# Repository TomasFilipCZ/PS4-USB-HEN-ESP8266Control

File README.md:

<h1 align="center">PS4 USB HEN Controlled by ESP8266</h1>

<p>Small electronic board to support automatic loading HEN in PS4 with ESP8266. Project using method discovered on PS4 Firmware 9.00, where user need manually plug USB flash drive in right time to load HEN. 

Together with  ESP8266 as WebServer is PS4-USB-HEN  controlling power supply for USB drive, causing automatic loading HEN in desired time without user interaction.  

Project is modification of "PS4 Server 9.00", aim is to share design data of small PCB to create device for wide  usage of automatic loading and implement basic electronic protection for PS4.  </p>

<i>Status</i>
<b> 23.01.2022 waiting for PCB from production to add more picture and check design files !</b>

## Project requirements
- [ Wemos ESP8266 Mini Board ](https://www.wemos.cc/en/latest/d1/d1_mini_lite.html "v3.00") or any available clone supporting 4MB Flash, recommend is use version V3 with mounting holes as listed in pictures section below
- any working USB 2.0 Flash Disk ( size basically not matter >128MBytes, USB3.0 is not required)
-  Micro USB 2.0 data cable ( is recommend to not exceed length of 1.8M )

## Links
ESP8266 needs firmware to run WebServer with DHCP/DNS service, it can be found here:
- Either compile slight mod of PS4-Server-900 with USB Auto mount feature [PS4-Server-900u](https://github.com/stooged/PS4-Server-900u "<project-name>use pico-exfat")
or download binary file "ESP8266 Auto mount USB 900NA.bin"  from [compiled version by Karo (Twitter karo_sharifi ) ](https://t.co/9buavulD5x "900u.bin")

USB Drive for PS4-USB-HEN needs to be properly installed with ChendoChap Kernel Exploit 
- [ChendoChap PS4 9.00 Kernel Exploit](https://github.com/ChendoChap/pOOBs4 "pico-exfat")

## Setup
- Setup once USB Flash disk
Instructions can be found on ChendoChap PS4 GitHub or generally on internet, alternatively to Win32Disk Imager can be recommend [Rufus utility](https://rufus.ie/en/ "Rufus")   in both solution choose as USB Image  <b>exfathax_pico.img file</b>. 

- Setup once ESP8266
Either by Arduino IDE or [NodeMCU-PyFlasher](https://github.com/marcelstoer/nodemcu-pyflasher/releases), manual for programming ESP8266 with USB cable with PC can be find easily on internet. (with USB cable plug into ESP8266 board)

- Plug ESP8266 Board into PS4-USB-HEN, micro USB cable to PS4 and PS4-USB_HEN micro USB port. Due Webserver/DNS capability of ESP8266 web page with HEN  can be access through 'User Guide/Helpful Info' in PS4  <i>(required successful Wifi connection to ESP8266, if is not changed, access point is 'PS4_WEB_AP' , password is 'password' or '12345678</i> )

## Pictures

## Project structure

- PCB Design data are developed in KiCad 5.1.10
- directory <b>bom</b> contains JLCPCB compatible BOM and BOM with MPN parts, including order codes from [TME.EU](https://tme.eu)
- directory <b>gerber</b> contains gerbers files with pick-up place file. Components are located only in TOP layer. USB A connector hasn't defined positions because is THT. 
- directory <b>libs </b> contains project specific  library special thanks to [ Raoul Rubien, for library for Wemos D1 Mini]( https://github.com/rubienr/wemos-d1-mini-kicad) and [ Fork Sand Devloper ](https://gitlab.com/forksand-dev1) for 3Dmodel of USB-A connector

## Future Updates

- [ ] Create STEP/STL Model of Plastic BOX to be able printed in 3D Printer
- [ ] Waiting for Delivering PCB to test all complete designs - <b> design is not tested YET! </b>

## Author

**Tomas Filip**

- [Profile](https://github.com/TomasFilipCZ "Tomas Filip on GitHub")
- [Join us on Discord](https://discord.gg/DWephJvzwR "Discord Server")

## 🤝 Support

Contributions, issues, and feature requests are welcome!

if you like this project, stay tuned !

<i>Special thanks: Karo, ChendoChap, stooged for their work and thanks to all community helper and developer on PS scene.  It's really fun...</i>

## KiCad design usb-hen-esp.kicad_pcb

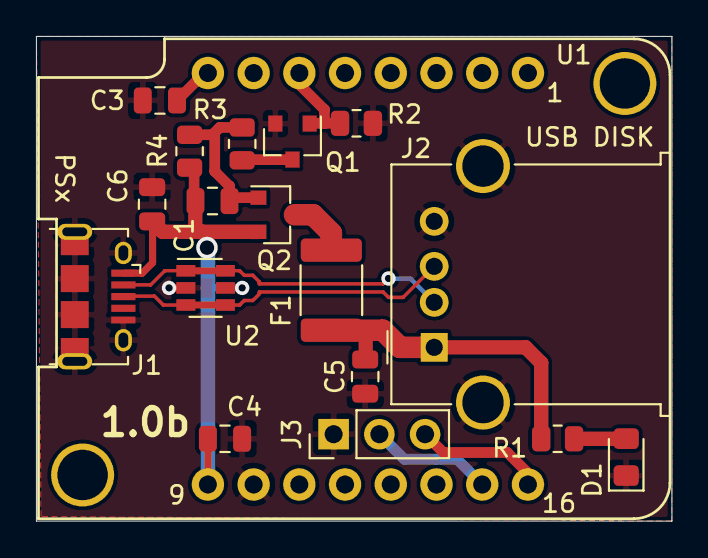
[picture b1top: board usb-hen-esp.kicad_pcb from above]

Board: 2 copper layers, 35.3 x 26.9 mm, 18 parts (0 on the bottom side), 13 nets.

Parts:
C1, C3, C4, C5: 100nF; C_0805_2012Metric
C6: 22uF_25V; C_0805_2012Metric
D1: D_LED_0805_0805; LED_0805_2012Metric_Pad1.15x1.40mm_HandSolder
F1: Polyfuse_16V_1.1A; Fuse_1812_4532Metric_Pad1.30x3.40mm_HandSolder
J1: USB_B_Micro; USB_Micro-Jing Extension
J2: USB_A; USB_A_Molex_67643_Horizontal
J3: HEADER-2.54-3pin-Vertical; PinHeader_1x03_P2.54mm_Vertical
Q1: 2N7002; SOT-23
Q2: AO3401A; SOT-23
R1: 330R; R_0805_2012Metric
R2, R4: 100k; R_0805_2012Metric
R3: 10k; R_0805_2012Metric
U1: WeMos_D1_mini; wemos-d1-mini-connectors-only
U2: USBLC6-2SC6; SOT-23-6

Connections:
+3V3: C3.1, U1.8
+5V: C1.1, C4.1, C6.1, J1.1, Q2.2, R4.1, U1.9, U2.5
+5VP: C5.2, F1.2, J2.1, R1.1
/UART_RX: J3.2, U1.15
/UART_TX: J3.3, U1.16
/USBP: Q1.1, R2.1, U1.6
/USB_D+: J1.3, J2.3, U2.3, U2.4
/USB_D-: J1.2, J2.2, U2.1, U2.6
GND: C3.2, C4.2, C5.1, C6.2, D1.1, J1.5, J1.6, J2.4, J2.5, J3.1, Q1.2, R2.2, U1.10, U2.2
unnamed: C1.2, Q2.1, R3.1, R4.2
unnamed: D1.2, R1.2
unnamed: F1.1, Q2.3
unnamed: Q1.3, R3.2

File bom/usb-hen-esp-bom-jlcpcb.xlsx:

Comment | Designator | Footprint | LCSC Part #
100nF | C1, C3, C4, C5 | 0805_C | C49678
22uF_25V | C6 | 0805_C | C45783
D_LED_0805_0805 | D1 | 0805_D | C2297
Polyfuse_16V_1.1A | F1 | 1812_FUSE | C70114
USB_B_Micro | J1 | Connector_USB:USB_Micro-B_Molex-105017-0001 | C10418
USB_A | J2 | Connector_USB:USB_A_Molex_67643_Horizontal | C2345
2N7002 | Q1 | SOT-23 | C8545
AO3401A | Q2 | SOT-23 | C15127
330R | R1 | 0805_R | C17630
100k | R2, R4 | 0805_R | C17407
10k | R3 | 0805_R | C17414
USBLC6-2SC6 | U2 | SOT-23-6 | C2827654

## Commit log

2022-01-23 fix formating in readme
2022-01-25 slightly update silkscreen for the text and add discord invitation
